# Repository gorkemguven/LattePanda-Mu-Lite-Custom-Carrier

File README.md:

# 🐼 Custom LattePanda Mu Lite Carrier Board - Complete Hardware Implementation

## 📖 Project Overview & Engineering Scope
This repository hosts a **fully custom-engineered 4-layer PCB layout, physical routing, and mechanical integration** for the **LattePanda Mu Lite Carrier Board**. 

While the core electrical connectivity references the open-source hierarchical schematic architecture provided by DFRobot for compatibility with the **LattePanda Mu Compute Module** (an x86 processor module featuring integrated RAM and eMMC), **100% of the physical board implementation, trace impedance/width calculations, component footprint verification, 3D mechanical alignment, and high-speed signal routing were executed from scratch by Görkem Güven.**

Designing a carrier board for an x86 compute module is not a simple point-to-point routing task; it requires strict adherence to high-speed design rules, power delivery network (PDN) stability, electrostatic discharge (ESD) protection strategies, and precise mechanical tolerances. Every single trace, via, copper pour, and component placement on this board has been meticulously calculated and manually routed.

---

## 🖼️ 3D PCB Renders & Physical Layout Analysis

Below are the 3D mechanical and copper-routed views generated directly from KiCad, showcasing the placement topology and signal distribution across the board:

| Top View (`Latte_panda_mu_3D_top.png`) | Bottom View (`Latte_panda_mu_3D_bottom.png`) |
| :---: | :---: |
|  |  |

### 🔍 Top View Architectural Breakdown (`Latte_panda_mu_3D_top.png`)
- **Compute Module Core (`A1` Socket & Mechanical Mounting):** Located in the central-right zone, the high-density dual-row SMD connector (`A1`) interfaces directly with the LattePanda Mu module. To the far right, two **M2x5.5 SMT nuts (`H5`, `H6`)** are aligned within the module's mechanical outline to securely anchor the x86 board without inducing mechanical stress on the SMD pins.
- **Dual M.2 Expansion Slots (Top Center):** Two vertical 30mm M.2 sockets (`J15` and `J16`) are positioned at the upper edge with dedicated mounting standoffs, routed with length-matched differential pairs directly from the `A1` socket for high-speed NVMe/PCIe and wireless connectivity.
- **Perimeter I/O Coastline (Left Edge):** All external user-facing connectors are cleanly aligned along the left board edge for seamless enclosure integration:
  - **Top-Left (`J4`):** Dual-Stacked USB 3.0 Type-A receptacle (blue insert) backed by ultra-low capacitance ESD arrays (`U3`, `U5`).
  - **Upper-Mid Left (`J6`):** Gigabit Ethernet RJ45 Magjack (`RB1-125B8G1A`) paired directly with the Ethernet controller IC (`U6`), crystal oscillator (`Y1`), and termination passives.
  - **Mid-Left (`J5`):** Dual-Stacked USB 2.0 Type-A receptacle protected by 6V/1A polyfuses (`F2`, `F3`), bulk capacitance (`C30`), and a `D3V3XA4B10LP` TVS diode array (`U4`).
  - **Lower-Mid Left (`J3`):** HDMI output port with dedicated level-shifting and inline ESD protection along the TMDS differential lanes.
- **Power Delivery Network - PDN (Bottom-Left):** Features the primary power inputs (`J17`, `J18`) feeding two isolated high-efficiency DC-DC synchronous buck converter stages (`U15`/`L1` and `U16`/`L2`). Surrounded by high-current power inductors, Schottky diodes, and dense input/output capacitor banks (`C64`–`C83`) to guarantee low-ripple voltage rails under heavy x86 CPU loads.
- **System Control, RTC & Headers (Top-Right & Bottom-Right):** Includes a coin-cell RTC battery holder (top-right), tactile power/reset buttons (`SW1`, `SW2` at top-left), PWM fan connector, and dual-row GPIO expansion headers along the bottom-right perimeter.

### 🔍 Bottom View Architectural Breakdown (`Latte_panda_mu_3D_bottom.png`)
- **Continuous Ground Reference Plane (`B.Cu`):** The bottom layer is predominantly flooded with a solid, low-impedance `GND` copper pour, stitched extensively with ground vias to provide clean return paths and EMI shielding for the high-speed signals routed on the top and inner layers.
- **Impedance-Controlled Escape Routing:** Displays secondary differential pair breakouts and impedance-matched traces escaping from the central `A1` compute socket area toward the M.2 slots and peripheral headers, avoiding unnecessary layer transitions.
- **Through-Hole Mechanical Anchoring & Isolation:** Clearly exhibits the staggered 18-pin THT footprint of the Dual USB 3.0 port, the 8-pin + shield tabs of the Dual USB 2.0 port, the RJ45 Magjack pin array, and the four corner mounting holes (`H1`–`H4`) with exposed ground-ring pads for chassis grounding.

---

## ⚙️ Deep-Dive: Engineering & Design Process

Throughout the development of this carrier board, several critical hardware engineering challenges were analyzed and resolved:

### 1. High-Speed Signal Integrity & 4-Layer Stackup Routing
The LattePanda Mu module exposes high-speed interfaces including **PCIe Gen 3.0 (x4)**, **USB 3.0 (SuperSpeed 5Gbps)**, **USB 2.0**, **Gigabit Ethernet (MDI)**, and **HDMI/DisplayPort**.
- **Differential Pair Routing:** All high-speed differential pairs (`USB3_TX/RX`, `USB2_D+/D-`, `PCIe`, `HDMI`, and `Ethernet`) were manually routed with strict length matching, phase tuning, and symmetrical geometry to prevent signal skew and electromagnetic interference (EMI).
- **Reference Planes:** A dedicated 4-layer stackup was utilized to ensure continuous, unbroken Ground (`GND`) reference planes directly beneath high-speed traces, minimizing return path inductance and crosstalk.

### 2. Custom Footprint Verification & Multi-Source 3D CAD Integration
Standard library footprints often fail to represent complex multi-port connectors accurately. A major phase of this project involved auditing pinouts, verifying mechanical datasheets, and integrating accurate 3D STEP models:
- **LattePanda Mu A1 Compute Socket:** Configured the dense dual-row SMD connector (`A1`) alongside precise mechanical alignment for the module's **M2x5.5 SMT mounting nuts (`H5`, `H6`)**. Imported and manually calibrated the X-Y-Z offsets and rotation axes of the physical compute module's 3D CAD model to verify vertical and horizontal component clearances under the module.
- **Dual-Stacked USB 3.0 Type-A (`J4` / 18-Pin):** Standard component search engines frequently misrepresent stacked connectors with single-port 3D models. Cross-referenced multiple industrial part numbers (including **Amphenol `GSB311131HR`**, **Molex `48408-0003`**, **TE `1932799-1`**, and **Würth `692212030100`**), verified the 18-pin dual-row staggered through-hole footprint + 4 mechanical shield tabs, and integrated a true dual-stacked STEP model.
- **Dual-Stacked USB 2.0 Type-A (`J5`):** Verified the 8-pin dual-port power and data architecture (`VBUS1/2`, `D1+/D1-`, `D2+/D2-`) paired with dedicated polyfuse overcurrent protection (`F2`, `F3` - 6V/1A) and bulk decoupling (`22uF/10V`).
- **Gigabit Ethernet Magjack (`RB1-125B8G1A`):** Sourced and aligned the UDE integrated transformer RJ45 connector with built-in status LEDs, ensuring proper isolation clearance between the chassis ground and digital ground.

### 3. Electrostatic Discharge (ESD) & Power Protection Architecture
External I/O ports are highly vulnerable to transient voltage spikes and human-body ESD events. To ensure industrial-grade reliability:
- **Ultra-Low Capacitance TVS Arrays (`D3V3XA4B10LP`):** Placed directly adjacent to the USB connectors in a flow-through routing topology. This minimizes stub length and clamps transient voltages on `CON_USB1_D_P/N` and `CON_USB2_D_P/N` lines before they can reach the x86 compute module.
- **Compact 0402 ESD Protection (`ESD5V0B03`):** Integrated 0402 metric package bidirectional TVS diodes across auxiliary I/O and control lines, optimizing board real estate without compromising protection.

### 4. Design for Manufacturing (DFM) & Design Rule Check (DRC) Resolution
A board that only looks good in CAD is useless if it fails on the SMT assembly line. Extensive DRC and DFM audits were conducted to make the board production-ready:
- **Optical Fiducial Marker Clearance (`FID1`, `FID2`, `FID3`):** Resolved critical *"Front solder mask aperture bridges items with different nets"* errors. Because fiducial markers are un-netted copper pads (`<no net>`), the surrounding `GND` copper pours across `F.Cu` and inner layers were encroaching on the solder mask opening. Custom local copper clearance rules were applied to pull back the `GND` zone, ensuring high-contrast optical recognition for automated Pick-and-Place (SMT) vision systems.
- **Mechanical Courtyard Overlaps (`A1` vs `H5`/`H6`):** Analyzed and validated the intentional courtyard intersections between the LattePanda Mu's overarching mechanical boundary (`A1`) and the structural SMT securing nuts (`H5`, `H6`).

---

## 🧩 Modular Hierarchical Architecture
The electrical design is organized into clean, modular hierarchical schematic sheets to separate power domains and high-speed subsystems:

| Schematic Sheet | Subsystem Description |
| :--- | :--- |
| `LattePandaMu_carrier_custom.kicad_sch` | Top-level master sheet mapping global labels and hierarchical interconnects. |
| `LattePanda_Module.kicad_sch` | Core A1 high-density connector pinout mapping for the x86 module. |
| `psu.kicad_sch` | Power Supply Unit, DC-DC buck converters, voltage rails, and power sequencing. |
| `usb_2_3.kicad_sch` | USB 3.0 SuperSpeed & USB 2.0 host controllers, VBUS protection, and ESD arrays. |
| `ethernet.kicad_sch` | Gigabit Ethernet MDI routing, magnetics termination, and RJ45 LED interface. |
| `pciex4.kicad_sch` | High-speed PCIe Gen3 x4 lane routing and AC coupling capacitors. |
| `m2_em_key.kicad_sch` | M.2 E-Key / M-Key socket implementation for NVMe SSD and wireless expansion. |
| `hdmi.kicad_sch` | TMDS differential video routing, level shifting, and HPD/DDC protection. |
| `gpio.kicad_sch` & `fan.kicad_sch` | Active thermal management (PWM fan control) and general-purpose I/O headers. |

---

## 📂 Repository File Structure

```text
├── production/
│   ├── Gerber_Latte_panda.zip                 # Ready-to-manufacture Gerber & Excellon Drill files
│   └── bom.csv                                # Complete Bill of Materials (BOM) for SMT assembly
├── Libraries/                                 # Project-specific custom footprints, symbols, and 3D STEP models
├── LattePandaMu_carrier_custom_Sch.pdf        # Complete searchable PDF of all hierarchical schematics
├── Latte_panda_mu_3D_top.png                  # High-resolution 3D render (Top View)
├── Latte_panda_mu_3D_bottom.png               # High-resolution 3D render (Bottom View)
├── Latte_panda_mu_Footprint_Layer_1.png       # Layer 1 (F.Cu - Top Signal & Component Layer)
├── Latte_panda_mu_Footprint_Layer_2.png       # Layer 2 (In1.Cu - Internal Ground/Power Plane)
├── Latte_panda_mu_Footprint_Layer_3.png       # Layer 3 (In2.Cu - Internal Signal/Power Plane)
├── Latte_panda_mu_Footprint_Layer_4.png       # Layer 4 (B.Cu - Bottom Signal & Decoupling Layer)
├── LattePandaMu_carrier_custom.kicad_pro      # KiCad Project File
├── LattePandaMu_carrier_custom.kicad_pcb      # Custom 4-Layer PCB Layout File
├── *.kicad_sch                                # Main and sub-sheet hierarchical schematic files
└── fp-lib-table & sym-lib-table               # Library mapping tables
```

---

## 🖼️ 4-Layer Copper Routing Breakdown

| Layer 1 (Top Copper - `F.Cu`) | Layer 2 (Inner Plane 1 - `In1.Cu`) |
| :---: | :---: |
|  |  |
| **Layer 3 (Inner Plane 2 - `In2.Cu`)** | **Layer 4 (Bottom Copper - `B.Cu`)** |
|  |  |

---

## ⚠️ Hardware Disclaimer

> [!WARNING]
> **Please Read Carefully Before Manufacturing:**  
> This project was developed as an intensive hardware engineering, high-speed PCB layout, and CAD implementation study. While the board passes all Design Rule Checks (DRC), impedance calculations, and mechanical verifications in KiCad, **it has not been physically fabricated or bench-tested yet.**
> 
> The design files and Gerbers are provided **"AS IS"** without warranty of any kind. Anyone wishing to order PCBs from a fabrication house (e.g., JLCPCB, PCBWay) does so entirely at their own risk.

---

## 📜 Attribution & Licensing
- **Electrical Reference:** The base connectivity follows the open-source specifications of the [DFRobot LattePanda Mu Lite Carrier](https://github.com/LattePandaTeam/LattePanda-Mu).
- **PCB Engineering, Calculations & Layout:** 100% custom designed, routed, and verified by **Görkem Güven**.

This open-source hardware project is released under the **MIT License**. You are free to study, modify, and distribute the files provided that proper attribution is given to the author.

---

## 👨‍💻 Author & Contact
**Görkem Güven**  
*B.Sc. in Electrical and Electronics Engineering — Muğla Sıtkı Koçman University (GPA: 3.44 / 4.00)*  

Hardware Design Engineer focusing on Embedded Systems, Power Electronics (SMPS), and High-Speed Multi-Layer PCB Layout.  
- 🐙 **GitHub:** [@gorkemguven](https://github.com/gorkemguven)

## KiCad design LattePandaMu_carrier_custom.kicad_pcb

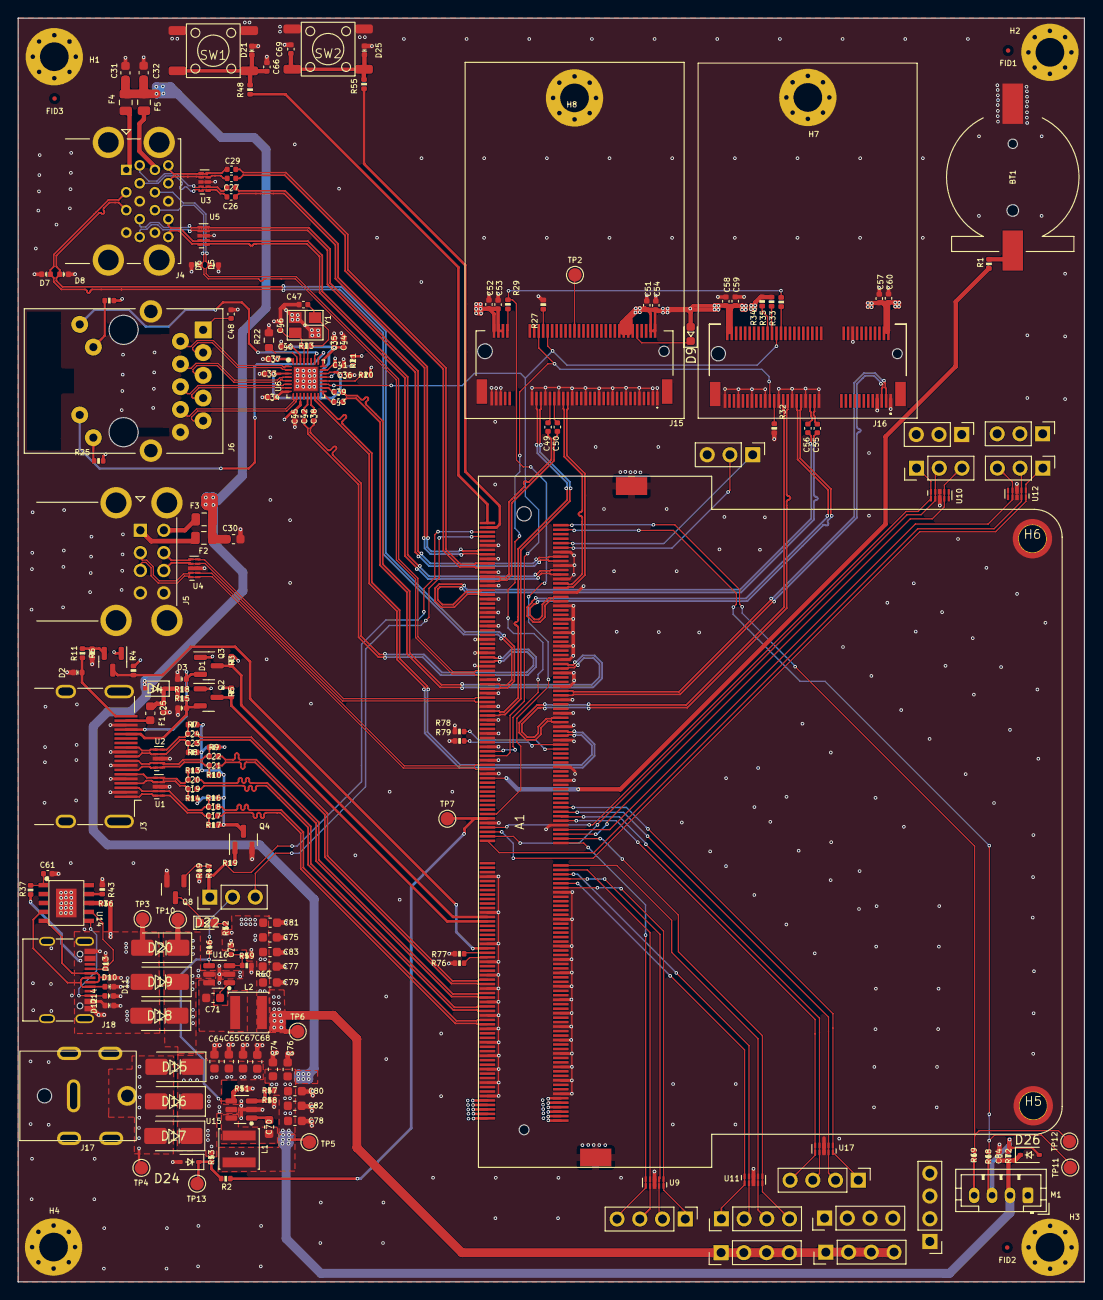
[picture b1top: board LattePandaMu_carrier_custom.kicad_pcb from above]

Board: 4 copper layers, 119.1 x 141.2 mm, 216 parts (0 on the bottom side), 173 nets.

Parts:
A1: LattePanda_Mu; LattePanda_Module_H8.0mm_Horizontal
BT1: Battery_Cell; Battery_Holder_CR1220_S8411-45R
C17, C18, C19, C20, C21, C22, C23, C24, C25, C26, C27, C28, C29, C33, C34, C35, C36, C37, C38, C39, C40, C41, C42, C43, C45, C48, C52, C54, C58, C60, C84: 100nF/50V; C_0402_1005Metric
C30, C31, C32, C64, C65, C67, C68, C74, C75, C76, C77, C80, C81, C82, C83: 22uF/10V; C_0603_1608Metric
C44, C51, C53, C57, C59: 10uF/50V; C_0402_1005Metric
C46, C47, C73: 12pF/50V; C_0402_1005Metric
C49, C50, C55, C56: 220nF/50V; C_0402_1005Metric
C61, C66, C69: 1uF/16V; C_0402_1005Metric
C70, C71: 100nF/50V; C_0603_1608Metric
C78, C79: 100nF/10V; C_0603_1608Metric
D1, D2, D3: ESD5V0B03; D_0402_1005Metric
D4, D26: 1N5819WS; D_SOD-323
D5, D6, D7, D8, D10, D11, D21, D25: ESD9B5.0ST5G; D_0402_1005Metric
D9: LED_G; LED_0603_1608Metric
D12, D13, D14: D_Zener; D_0402_1005Metric
D15, D16, D17, D18, D19, D20: D_Schottky; D_SMA
D22: LED; LED_0603_1608Metric
D24: 3V3 Izt=5mA; D_SOD-323
F1: 6V/50mA; C_0603_1608Metric
F2, F3, F4, F5: 6V/1A; Fuse_0805_2012Metric
FID1, FID2, FID3: Fiducial; Fiducial_0.5mm_Mask1mm
H1, H2, H3, H4, H7, H8: MountingHole_Pad; MountingHole_3.2mm_M3_Pad_Via
H5, H6: MountingHole_Pad; MountingHole_3mm_M2_Pad_TopOnly
J1, J8, J10, J11, J14: Conn_01x03_Pin; PinHeader_1x03_P2.54mm_Vertical
J3: HDMI_A; HDMI_A_Molex_208658-1001_Horizontal
J4: USB3_A_Stacked; USB3_A_Molex_48406-0001_Horizontal_Stacked
J5: USB_A_Stacked; USB_A_CUI_UJ2-ADH-TH_Horizontal_Stacked
J6: RJ45_RB1-125B8G1A; RJ45_UDE_RB1-125B8G1A
J7, J9, J12, J13, J19, J20, J21: Conn_01x04_Pin; PinHeader_1x04_P2.54mm_Vertical
J15: Bus_M.2_Socket_M; PCIe_M.2_Connectors_P=0.5mm_H=4.2mm_KeyM
J16: Bus_M.2_Socket_E; PCIe_M.2_Connectors_P=0.5mm_H=4.2mm_KeyE
J17: Barrel_Jack_Switch; DC_Jack_DC007B_30V_10A
J18: USB_C_Receptacle_USB2.0_16P; USB_C_Receptacle_G-Switch_GT-USB-7010ASV
JP1: Jumper_3_Bridged12; PinHeader_1x03_P2.54mm_Vertical
L1, L2: 2.2uH/4.3A; L_Sunlord_SWPA4020S
M1: Fan_4pin; JST_PH_B4B-PH-K_1x04_P2.00mm_Vertical
Q1, Q8: 2N7002; SOT-23
Q2, Q3, Q4: 2SK3018; SOT-23
R1, R11, R37, R47: 1K/1%; R_0402_1005Metric
R2, R20, R21, R34, R35, R36, R49, R58, R78, R79: 10K/1%; R_0402_1005Metric
R3, R5, R15, R18, R19, R52, R53: 2.2K/1%; R_0402_1005Metric
R4, R23: 1M/1%; R_0402_1005Metric
R6, R59, R68: 21.5K/1%; R_0402_1005Metric
R7, R8, R9, R10, R13, R14, R16, R17, R24, R25: 470R/1%; R_0402_1005Metric
R22: 2.49K/1%; R_0603_1608Metric
R27, R29, R32, R33: 0R/1%; R_0402_1005Metric
R43: 56K/1%; R_0402_1005Metric
R46, R51, R76, R77: 100K/1%; R_0402_1005Metric
R48, R55, R69: 100R/1%; R_0402_1005Metric
R57: 75K/1%; R_0402_1005Metric
R60, R72: 4.7K/1%; R_0402_1005Metric
SW1, SW2: SW_Push; SW_Push_6x6x6
TP2, TP3, TP4, TP5, TP6, TP7, TP10, TP11, TP12, TP13: TestPoint; TestPoint_Pad_D1.5mm
U1, U2, U3, U4, U5: D3V3XA4B10LP; Diodes_UDFN-10_1.0x2.5mm_P0.5mm
U6: RTL8111H-CG-RH; QFN-32-1EP_4x4mm_P0.4mm_EP2.65x2.65mm
U9, U10, U11, U12, U17: ULC0524P; Diodes_UDFN-10_1.0x2.5mm_P0.5mm
U14: USB PD等快充协议受电芯片-CH224K-ESSOP10; ESSOP-10-1EP_3.9x5mm_P1.0mm_EP3.2x2.3
U15, U16: LM2734X; TSOT-23-6
Y1: 25MHz; Crystal_SMD_3225-4Pin_3.2x2.5mm

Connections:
5V_HDMI_VCC: C25.1, D4.1 (K), F1.1, R15.1, R18.1
+1V0: C33.2, C34.2, C35.2, C36.2, C40.2, C44.2, U6.3 (AVDD10), U6.8 (AVDD10), U6.22 (DVDD10), U6.24 (REGOUT), U6.30 (AVDD10)
+3V3: C37.2, C41.2, C45.2, C51.2, C52.2, C53.2, C54.2, C57.2, C58.2, C59.2, C60.2, C73.1, C75.1, C77.1, C79.1, C81.1, C83.1, D9.2 (A), J13.1, J13.2, J13.3, J13.4, J14.1, J14.2, J14.3, J15.2 (3.3V), J15.4 (3.3V), J15.12 (3.3V), J15.14 (3.3V), J15.16 (3.3V), J15.18 (3.3V), J15.70 (3.3V), J15.72 (3.3V), J15.74 (3.3V), J16.2 (3.3V), J16.4 (3.3V), J16.72 (3.3V), J16.74 (3.3V), J21.1, J21.2, J21.3, J21.4, L2.2, Q1.1 (G), Q2.1 (G), Q3.1 (G), R3.1, R4.1, R5.1, R20.2, R21.2, R24.2, R25.2, R34.2, R35.2, R52.1, R59.2, TP6.1 (1_1), U6.11 (AVDD33), U6.23 (VDDREG), U6.32 (AVDD33)
+5V: C30.2, C31.2, C32.2, C74.1, C76.1, C78.1, C80.1, C82.1, C84.1, D4.2 (A), D26.1 (K), F2.1, F3.1, F4.1, F5.1, L1.2, M1.2 (+), R57.2, R72.1, TP5.1 (1_1)
+12V: D15.2 (A), D16.2 (A), D17.2 (A), J17.1, TP4.1 (1_1)
+15V: D12.1 (K), D18.2 (A), D19.2 (A), D20.2 (A), J18.A4 (VBUS), J18.A9 (VBUS), J18.B4 (VBUS), J18.B9 (VBUS), R36.1, R37.1, TP3.1 (1_1)
+BATT: A1.115 (VBAT), R1.2
/Fan/FAN_1_PWM: A1.2 (FAN1_PWM), R69.1, TP12.1 (1_1)
/Fan/FAN_1_TAC: A1.4 (FAN1_TAC), R68.1, TP11.1 (1_1)
/GPIO/GPP_D0: A1.128 (GPP_D0), J19.1, U17.1, U17.10 (NC)
/GPIO/GPP_D1: A1.130 (GPP_D1), J19.2, U17.2, U17.9 (NC)
/GPIO/GPP_D2: A1.132 (GPP_D2), J19.3, U17.4, U17.7 (NC)
/GPIO/GPP_D3: A1.134 (GPP_D3), J19.4, U17.5, U17.6 (NC)
/GPIO/I2C2_SCL: A1.154 (I2C2_SCL), J9.1, U11.1, U11.10 (NC)
/GPIO/I2C2_SDA: A1.156 (I2C2_SDA), J7.1, U9.1, U9.10 (NC)
/GPIO/I2C3_SCL: A1.150 (I2C3_SCL), J9.2, U11.2, U11.9 (NC)
/GPIO/I2C3_SDA: A1.152 (I2C3_SDA), J7.2, U9.2, U9.9 (NC)
/GPIO/I2C4_SCL: A1.146 (I2C4_SCL), J9.3, U11.4, U11.7 (NC)
/GPIO/I2C4_SDA: A1.148 (I2C4_SDA), J7.3, U9.4, U9.7 (NC)
/GPIO/I2C5_SCL: A1.142 (I2C5_SCL), J9.4, U11.5, U11.6 (NC)
/GPIO/I2C5_SDA: A1.144 (I2C5_SDA), J7.4, U9.5, U9.6 (NC)
/GPIO/SOC_UART0_RX: A1.137 (UART0_RXD), J8.1, U10.1, U10.10 (NC)
/GPIO/SOC_UART0_TX: A1.139 (UART0_TXD), J10.1, U12.1, U12.10 (NC)
/GPIO/SOC_UART1_RX: A1.141 (UART1_RXD), J8.2, U10.2, U10.9 (NC)
/GPIO/SOC_UART1_TX: A1.143 (UART1_TXD), J10.2, U12.2, U12.9 (NC)
/GPIO/SOC_UART2_RX: A1.140 (UART2_RXD), J8.3, U10.4, U10.7 (NC)
/GPIO/SOC_UART2_TX: A1.138 (UART2_TXD), J10.3, U12.4, U12.7 (NC)
/Gigabit Ethernet/GbE_PCIe_CLK+: A1.94 (REFCLK4+), U6.15 (REFCLK_P)
/Gigabit Ethernet/GbE_PCIe_CLK-: A1.96 (REFCLK4-), U6.16 (REFCLK_N)
/Gigabit Ethernet/GbE_PCIe_RX+: A1.64 (HSIO6_RX+), C43.2
/Gigabit Ethernet/GbE_PCIe_RX-: A1.66 (HSIO6_RX-), C39.2
/Gigabit Ethernet/GbE_PCIe_TX+: A1.61 (HSIO6_TX+), C42.2
/Gigabit Ethernet/GbE_PCIe_TX-: A1.63 (HSIO6_TX-), C38.2
/Gigabit Ethernet/HSI+: C42.1, U6.13 (HSIP)
/Gigabit Ethernet/HSI-: C38.1, U6.14 (HSIN)
/Gigabit Ethernet/HSO+: C43.1, U6.17 (HSOP)
/Gigabit Ethernet/HSO-: C39.1, U6.18 (HSON)
/Gigabit Ethernet/MDI0+: J6.R2 (TD1+), U6.1 (MDIP0)
/Gigabit Ethernet/MDI0-: J6.R3 (TD1-), U6.2 (MDIN0)
/Gigabit Ethernet/MDI1+: J6.R4 (TD2+), U6.4 (MDIP1)
/Gigabit Ethernet/MDI1-: J6.R5 (TD2-), U6.5 (MDIN1)
/Gigabit Ethernet/MDI2+: J6.R6 (TD3+), U6.6 (MDIP2)
/Gigabit Ethernet/MDI2-: J6.R7 (TD3-), U6.7 (MDIN2)
/Gigabit Ethernet/MDI3+: J6.R8 (TD4+), U6.9 (MDIP3)
/Gigabit Ethernet/MDI3-: J6.R9 (TD4-), U6.10 (MDIN3)
/HDMI/DDC_SCL: D1.2 (A2), J3.15 (SCL), Q2.2 (S), R15.2
/HDMI/DDC_SDA: D3.2 (A2), J3.16 (SDA), Q3.2 (S), R18.2
/HDMI/DDI_B_DDC_SCL: A1.171 (DDIB_DDC_SCL), Q2.3 (D), R5.2
/HDMI/DDI_B_DDC_SDA: A1.169 (DDIB_DDC_SDA), Q3.3 (D), R3.2
/HDMI/DDI_B_HPD: A1.183 (DDIB_HPD), Q1.3 (D), R4.2
/HDMI/DDI_B_TX0+: A1.217 (DDIB_TX0+), C17.1
/HDMI/DDI_B_TX0-: A1.215 (DDIB_TX0-), C18.1
/HDMI/DDI_B_TX1+: A1.211 (DDIB_TX1+), C19.1
/HDMI/DDI_B_TX1-: A1.209 (DDIB_TX1-), C20.1
/HDMI/DDI_B_TX2+: A1.205 (DDIB_TX2+), C21.1
/HDMI/DDI_B_TX2-: A1.203 (DDIB_TX2-), C22.1
/HDMI/DDI_B_TX3+: A1.199 (DDIB_TX3+), C23.1
/HDMI/DDI_B_TX3-: A1.197 (DDIB_TX3-), C24.1
/HDMI/HPD: D2.2 (A2), J3.19 (HPD), R11.2
/HDMI/TMDS_CK+: C23.2, J3.10 (CK+), R8.2, U2.4, U2.7 (NC)
/HDMI/TMDS_CK-: C24.2, J3.12 (CK-), R7.2, U2.5, U2.6 (NC)
/HDMI/TMDS_D0+: C21.2, J3.7 (D0+), R10.2, U2.1, U2.10 (NC)
/HDMI/TMDS_D0-: C22.2, J3.9 (D0-), R9.2, U2.2, U2.9 (NC)
/HDMI/TMDS_D1+: C19.2, J3.4 (D1+), R14.2, U1.4, U1.7 (NC)
/HDMI/TMDS_D1-: C20.2, J3.6 (D1-), R13.2, U1.5, U1.6 (NC)
/HDMI/TMDS_D2+: C17.2, J3.1 (D2+), R17.2, U1.1, U1.10 (NC)
/HDMI/TMDS_D2-: C18.2, J3.3 (D2-), R16.2, U1.2, U1.9 (NC)
/LattePanda Module/HSIO_0_TX+: A1.13 (HSIO0_TX+), C27.1
/LattePanda Module/HSIO_0_TX-: A1.15 (HSIO0_TX-), C26.1
/LattePanda Module/HSIO_1_TX+: A1.19 (HSIO1_TX+), C29.1
/LattePanda Module/HSIO_1_TX-: A1.21 (HSIO1_TX-), C28.1
/LattePanda Module/HSIO_2_RX+: A1.28 (HSIO2_RX+), J15.43 (PERp0/SATA-B-)
/LattePanda Module/HSIO_2_RX-: A1.30 (HSIO2_RX-), J15.41 (PERn0/SATA-B+)
/LattePanda Module/HSIO_2_TX+: A1.25 (HSIO2_TX+), C49.1
/LattePanda Module/HSIO_2_TX-: A1.27 (HSIO2_TX-), C50.1
/LattePanda Module/HSIO_3_RX+: A1.34 (HSIO3_RX+), J16.41 (PERp0)
/LattePanda Module/HSIO_3_RX-: A1.36 (HSIO3_RX-), J16.43 (PERn0)
/LattePanda Module/HSIO_3_TX+: A1.31 (HSIO3_TX+), C55.1
/LattePanda Module/HSIO_3_TX-: A1.33 (HSIO3_TX-), C56.1
/LattePanda Module/REFCLK0+: A1.85 (REFCLK0+), J15.55 (REFCLKp)
/LattePanda Module/REFCLK0-: A1.87 (REFCLK0-), J15.53 (REFCLKn)
/LattePanda Module/REFCLK3+: A1.88 (REFCLK3+), J16.47 (REFCLKp0)
/LattePanda Module/REFCLK3-: A1.90 (REFCLK3-), J16.49 (REFCLKn0)
/LattePanda Module/SLS_S3: A1.7 (SLS_S3), JP1.3 (B)
/LattePanda Module/SUSCKL_WIFI: A1.131 (SUSCLK), R29.1, R33.2
/LattePanda Module/USB_2_P7+: A1.76 (USB2_P7+), J16.3 (USB_D+)
/LattePanda Module/USB_2_P7-: A1.78 (USB2_P7-), J16.5 (USB_D-)
/LattePanda Module/~PWR_SW: A1.1 (~PWRBTN), R48.1
/LattePanda Module/~RST_SW: A1.3 (~RSTBTN), R55.1
/M.2 M Key/CON_PCIE_TX0+: C55.2, J16.35 (PETp0)
/M.2 M Key/CON_PCIE_TX0-: C56.2, J16.37 (PETn0)
/M.2 M Key/CON_PCIE_TX1+: C49.2, J15.49 (PETp0/SATA-A+)
/M.2 M Key/CON_PCIE_TX1-: C50.2, J15.47 (PETn0/SATA-A-)
/M.2 M Key/~CLKREQE: J16.53 (~CLKREQ0), R32.1
/M.2 M Key/~CLKREQM: J15.52 (~CLKREQ), R27.1
/Power Supply/CC1: D13.1 (K), J18.A5 (CC1), U14.7 (CC1)
/Power Supply/CC2: D14.1 (K), J18.B5 (CC2), U14.6 (CC2)
/Power Supply/PWR_C_D+: D11.2 (A2), J18.A6 (D+), J18.B6 (D+), U14.4 (DP)
/Power Supply/PWR_C_D-: D10.2 (A2), J18.A7 (D-), J18.B7 (D-), U14.5 (DM)
/Power Supply/PWR_EN: R46.1, R51.2, U15.4 (EN), U16.4 (EN)
/USB 2.0 & 3.0/CON_USB1_D_N: A1.109 (USB2_P5-), J5.2 (D1-), U4.2, U4.9 (NC)
/USB 2.0 & 3.0/CON_USB1_D_P: A1.111 (USB2_P5+), J5.3 (D1+), U4.1, U4.10 (NC)
/USB 2.0 & 3.0/CON_USB2_D_N: A1.79 (USB2_P3-), J5.6 (D2-), U4.5, U4.6 (NC)
/USB 2.0 & 3.0/CON_USB2_D_P: A1.81 (USB2_P3+), J5.7 (D2+), U4.4, U4.7 (NC)
/USB 2.0 & 3.0/CON_USB3_D_N: A1.73 (USB2_P2-), D8.1 (A1), J4.2 (D1-)
/USB 2.0 & 3.0/CON_USB3_D_P: A1.75 (USB2_P2+), D7.1 (A1), J4.3 (D1+)
/USB 2.0 & 3.0/CON_USB3_SSRX_N: A1.18 (HSIO0_RX-), J4.5 (SSRX1-), U5.4, U5.7 (NC)
/USB 2.0 & 3.0/CON_USB3_SSRX_P: A1.16 (HSIO0_RX+), J4.6 (SSRX1+), U5.5, U5.6 (NC)
/USB 2.0 & 3.0/CON_USB3_SSTX_N: C26.2, J4.8 (SSTX1-), U3.1, U3.10 (NC)
/USB 2.0 & 3.0/CON_USB3_SSTX_P: C27.2, J4.9 (SSTX1+), U3.2, U3.9 (NC)
/USB 2.0 & 3.0/CON_USB4_D_N: A1.67 (USB2_P1-), D6.1 (A1), J4.11 (D2-)
/USB 2.0 & 3.0/CON_USB4_D_P: A1.69 (USB2_P1+), D5.1 (A1), J4.12 (D2+)
/USB 2.0 & 3.0/CON_USB4_SSRX_N: A1.24 (HSIO1_RX-), J4.14 (SSRX2-), U5.1, U5.10 (NC)
/USB 2.0 & 3.0/CON_USB4_SSRX_P: A1.22 (HSIO1_RX+), J4.15 (SSRX2+), U5.2, U5.9 (NC)
/USB 2.0 & 3.0/CON_USB4_SSTX_N: C28.2, J4.17 (SSTX2-), U3.4, U3.7 (NC)
/USB 2.0 & 3.0/CON_USB4_SSTX_P: C29.2, J4.18 (SSTX2+), U3.5, U3.6 (NC)
/~PLT_RST: A1.105 (~PLTRST), J15.50 (~PERST), J16.52 (~PERST0), U6.19 (PERSTB)
/~PWR_LED/~PSON: A1.5 (SLS_S0), JP1.1 (A), R19.1, R47.2
/~WAKE: A1.103 (~WAKE), J15.54 (~PEWAKE), J16.55 (~PEWAKE0)
GND: A1.11 (GND), A1.14 (GND), A1.17 (GND), A1.20 (GND), A1.23 (GND), A1.26 (GND), A1.29 (GND), A1.32 (GND), A1.35 (GND), A1.38 (GND), A1.41 (GND), A1.44 (GND), A1.47 (GND), A1.50 (GND), A1.53 (GND), A1.56 (GND), A1.59 (GND), A1.62 (GND), A1.65 (GND), A1.68 (GND), A1.71 (GND), A1.74 (GND), A1.77 (GND), A1.80 (GND), A1.83 (GND), A1.86 (GND), A1.89 (GND), A1.92 (GND), A1.95 (GND), A1.98 (GND), A1.101 (GND), A1.107 (GND), A1.110 (GND), A1.113 (GND), A1.116 (GND), A1.135 (GND), A1.136 (GND), A1.151 (GND), A1.158 (GND), A1.167 (GND), A1.170 (GND), A1.181 (GND), A1.182 (GND), A1.188 (GND), A1.189 (GND), A1.194 (GND), A1.195 (GND), A1.200 (GND), A1.201 (GND), A1.206 (GND), A1.207 (GND), A1.212 (GND), A1.213 (GND), A1.218 (GND), A1.219 (GND), A1.224 (GND), A1.225 (GND), A1.230 (GND), A1.231 (GND), A1.236 (GND), A1.237 (GND), A1.242 (GND), A1.243 (GND), A1.248 (GND), A1.249 (GND), A1.MP (Mountinge_Pads), BT1.2 (-), C25.2, C30.1, C31.1, C32.1, C33.1, C34.1, C35.1, C36.1, C37.1, C40.1, C41.1, C44.1, C45.1, C46.2, C47.2, C48.1, C51.1, C52.1, C53.1, C54.1, C57.1, C58.1, C59.1, C60.1, C61.1, C64.1, C65.2, C66.2, C67.1, C68.2, C69.2, C74.2, C75.2, C76.2, C77.2, C78.2, C79.2, C80.2, C81.2, C82.2, C83.2, C84.2, D1.1 (A1), D2.1 (A1), D3.1 (A1), D5.2 (A2), D6.2 (A2), D7.2 (A2), D8.2 (A2), D10.1 (A1), D11.1 (A1), D12.2 (A), D13.2 (A), D14.2 (A), D21.2 (A2), D24.2 (A), D25.2 (A2), H1.1 (1_1), H2.1 (1_1), H3.1 (1_1), H4.1 (1_1), H5.1 (1_1), H6.1 (1_1), H7.1 (1_1), H8.1 (1_1), J1.3, J3.2 (D2S), J3.5 (D1S), J3.8 (D0S), J3.11 (CKS), J3.17 (GND), J3.SH, J4.4 (GND1), J4.7 (DRAIN1), J4.13 (GND2), J4.16 (DRAIN2), J4.19 (SHIELD), J5.4 (GND1), J5.8 (GND2), J5.9 (Shield), J6.R10 (GND), J6.SH, J11.1, J11.2, J11.3, J12.1, J12.2, J12.3, J12.4, J15.1 (GND), J15.3 (GND), J15.9 (GND), J15.15 (GND), J15.21 (GND), J15.27 (GND), J15.33 (GND), J15.39 (GND), J15.45 (GND), J15.51 (GND), J15.57 (GND), J15.71 (GND), J15.73 (GND), J15.75 (GND), J16.1 (GND), J16.7 (GND), J16.18 (GND), J16.33 (GND), J16.39 (GND), J16.45 (GND), J16.51 (GND), J16.57 (GND), J16.63 (GND), J16.69 (GND), J16.75 (GND), J17.2, J17.3, J18.A1 (GND), J18.A12 (GND), J18.B1 (GND), J18.B12 (GND), J18.S1 (SHIELD), J20.1, J20.2, J20.3, J20.4, M1.1 (-), Q4.2 (S), Q8.2 (S), R6.2, R22.2, R27.2, R32.2, R43.2, R49.2, R51.1, R58.1, R60.1, R76.2, R77.2, R78.1, R79.1, SW1.2, SW2.2, U1.3 (VSS), U1.8 (VSS), U2.3 (VSS), U2.8 (VSS), U3.3 (VSS), U3.8 (VSS), U4.3 (VSS), U4.8 (VSS), U5.3 (VSS), U5.8 (VSS), U6.33 (GND), U9.3 (VSS), U9.8 (VSS), U10.3 (VSS), U10.8 (VSS), U11.3 (VSS), U11.8 (VSS), U12.3 (VSS), U12.8 (VSS), U14.0 (GND), U15.2 (GND), U16.2 (GND), U17.3 (VSS), U17.8 (VSS), Y1.2, Y1.4
unnamed: A1.12 (SIO_UART_RX), J1.2
unnamed: A1.10 (SIO_UART_TX), J1.1
unnamed: A1.187 (TCP0_HPD), R76.1
unnamed: A1.185 (TCP1_HPD), R77.1
unnamed: A1.133 (~BIOS_SEL), R2.1, TP7.1 (1_1)
unnamed: A1.100 (~CLKREQ3), R79.2
unnamed: A1.102 (~CLKREQ4), R78.2
unnamed: BT1.1 (+), R1.1
unnamed: D9.1 (K), J15.10 (DAS/~DSS/~LED1)
unnamed: C66.1, D21.1 (A1), R48.2, SW1.1
unnamed: D22.2 (A), R52.2
unnamed: D22.1 (K), Q8.3 (D)
unnamed: C69.1, D25.1 (A1), R55.2, SW2.1
unnamed: D26.2 (A), M1.3 (Tacho), R68.2, R72.2
unnamed: F1.2, J3.18 (+5V)
unnamed: F4.2, J4.1 (VBUS1)
unnamed: F5.2, J4.10 (VBUS2)
unnamed: F2.2, J5.1 (VBUS1)
unnamed: F3.2, J5.5 (VBUS2)
unnamed: C48.2, J6.R1 (CT)
unnamed: J6.L1, R25.1
unnamed: J6.L3, R24.1
unnamed: J15.38 (DEVSLP), TP2.1 (1_1)
unnamed: J15.68 (SUSCLK), R29.2
unnamed: J16.50 (SUSCLK), R33.1
unnamed: J16.56 (~W_DISABLE1), R34.1
unnamed: J16.54 (~W_DISABLE2), R35.1
unnamed: JP1.2 (C), R46.2
unnamed: M1.4 (PWM), R69.2
unnamed: Q1.2 (S), R6.1, R11.1
unnamed: Q4.3 (D), R7.1, R8.1, R9.1, R10.1, R13.1, R14.1, R16.1, R17.1
unnamed: Q4.1 (G), R19.2
unnamed: Q8.1 (G), R47.1, R49.1
unnamed: C47.1, R23.1, U6.28 (CKXTAL1), Y1.1
unnamed: C46.1, R23.2, U6.29 (CKXTAL2), Y1.3
unnamed: R20.1, U6.20 (ISOLATEB)
unnamed: R21.1, U6.21 (LANWAKEB)
unnamed: J6.L4, U6.26 (LED1)
unnamed: J6.L2, U6.25 (LED2)
unnamed: R22.1, U6.31 (RSET)
unnamed: U10.5, U10.6 (NC)
unnamed: U12.5, U12.6 (NC)
unnamed: R43.1, U14.9 (CFG1)
unnamed: R36.2, U14.8 (VBUS)
unnamed: C61.2, R37.2, U14.1 (VDD)
unnamed: C70.2, U15.1 (BOOST)
unnamed: R57.1, R58.2, U15.3 (FB)
unnamed: C70.1, L1.1, U15.6 (SW)
unnamed: C71.2, U16.1 (BOOST)
unnamed: C73.2, R59.1, R60.2, U16.3 (FB)
unnamed: C71.1, L2.1, U16.6 (SW)
VDC: A1.250 (VIN), A1.251 (VIN), A1.252 (VIN), A1.253 (VIN), A1.254 (VIN), A1.255 (VIN), A1.256 (VIN), A1.257 (VIN), A1.258 (VIN), A1.259 (VIN), A1.260 (VIN), C64.2, C65.1, C67.2, C68.1, D15.1 (K), D16.1 (K), D17.1 (K), D18.1 (K), D19.1 (K), D20.1 (K), R53.2, TP10.1 (1_1), U15.5 (VIN), U16.5 (VIN)
VPullup: D24.1 (K), R2.2, R53.1, TP13.1 (1_1)

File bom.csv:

Designator,Footprint,Quantity,Value,LCSC Part #
A1,LattePanda_Module_H8.0mm_Horizontal,1,LattePanda_Mu,
BT1,Battery_Holder_CR1220_S8411-45R,1,Battery_Cell,
"C17, C18, C19, C20, C21, C22, C23, C24, C25, C26, C27, C28, C29, C33, C34, C35, C36, C37, C38, C39, C40, C41, C42, C43, C45, C48, C52, C54, C58, C60, C84",0402,31,100nF/50V,
"C30, C31, C32, C64, C65, C67, C68, C74, C75, C76, C77, C80, C81, C82, C83",0603,15,22uF/10V,
"C44, C51, C53, C57, C59",0402,5,10uF/50V,
"C46, C47, C73",0402,3,12pF/50V,
"C49, C50, C55, C56",0402,4,220nF/50V,
"C61, C66, C69",0402,3,1uF/16V,
"C70, C71",0603,2,100nF/50V,
"C78, C79",0603,2,100nF/10V,
"D1, D2, D3",0402,3,ESD5V0B03,
"D10, D11, D21, D25, D5, D6, D7, D8",0402,8,ESD9B5.0ST5G,
"D12, D13, D14",0402,3,D_Zener,
"D15, D16, D17, D18, D19, D20",D_SMA,6,D_Schottky,
D22,0603,1,LED,
D24,D_SOD-323,1,3V3 Izt=5mA,
"D26, D4",D_SOD-323,2,1N5819WS,
D9,0603,1,LED_G,
F1,0603,1,6V/50mA,
"F2, F3, F4, F5",0805,4,6V/1A,
"J1, J10, J11, J14, J8",PinHeader_1x03_P2.54mm_Vertical,5,Conn_01x03_Pin,
"J12, J13, J19, J20, J21, J7, J9",PinHeader_1x04_P2.54mm_Vertical,7,Conn_01x04_Pin,
J15,PCIe_M.2_Connectors_P=0.5mm_H=4.2mm_KeyM,1,Bus_M.2_Socket_M,
J16,PCIe_M.2_Connectors_P=0.5mm_H=4.2mm_KeyE,1,Bus_M.2_Socket_E,
J17,DC_Jack_DC007B_30V_10A,1,Barrel_Jack_Switch,
J18,USB_C_Receptacle_G-Switch_GT-USB-7010ASV,1,USB_C_Receptacle_USB2.0_16P,
J3,HDMI_A_Molex_208658-1001_Horizontal,1,HDMI_A,
J4,USB3_A_Molex_48406-0001_Horizontal_Stacked,1,USB3_A_Stacked,
J5,USB_A_CUI_UJ2-ADH-TH_Horizontal_Stacked,1,USB_A_Stacked,
J6,RJ45_UDE_RB1-125B8G1A,1,RJ45_RB1-125B8G1A,
"L1, L2",L_Sunlord_SWPA4020S,2,2.2uH/4.3A,
M1,JST_PH_B4B-PH-K_1x04_P2.00mm_Vertical,1,Fan_4pin,
"Q1, Q8",SOT-23,2,2N7002,
"Q2, Q3, Q4",SOT-23,3,2SK3018,
"R1, R11, R37, R47",0402,4,1K/1%,
"R10, R13, R14, R16, R17, R24, R25, R7, R8, R9",0402,10,470R/1%,
"R15, R18, R19, R3, R5, R52, R53",0402,7,2.2K/1%,
"R2, R20, R21, R34, R35, R36, R49, R58, R78, R79",0402,10,10K/1%,
R22,0603,1,2.49K/1%,
"R23, R4",0402,2,1M/1%,
"R27, R29, R32, R33",0402,4,0R/1%,
R43,0402,1,56K/1%,
"R46, R51, R76, R77",0402,4,100K/1%,
"R48, R55, R69",0402,3,100R/1%,
R57,0402,1,75K/1%,
"R59, R6, R68",0402,3,21.5K/1%,
"R60, R72",0402,2,4.7K/1%,
"SW1, SW2",SW_Push_6x6x6,2,SW_Push,
"TP10, TP11, TP12, TP13, TP2, TP3, TP4, TP5, TP6, TP7",TestPoint_Pad_D1.5mm,10,TestPoint,
"U1, U2, U3, U4, U5",Diodes_UDFN-10_1.0x2.5mm_P0.5mm,5,D3V3XA4B10LP,
"U10, U11, U12, U17, U9",Diodes_UDFN-10_1.0x2.5mm_P0.5mm,5,ULC0524P,
U14,ESSOP-10-1EP_3.9x5mm_P1.0mm_EP3.2x2.3,1,USB PD等快充协议受电芯片-CH224K-ESSOP10,
"U15, U16",TSOT-23-6,2,LM2734X,
U6,QFN-32-1EP_4x4mm_P0.4mm_EP2.65x2.65mm,1,RTL8111H-CG-RH,
Y1,Crystal_SMD_3225-4Pin_3.2x2.5mm,1,25MHz,

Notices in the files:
README.md:
License: MIT
